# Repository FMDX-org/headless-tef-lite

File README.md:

# TEF668X Headless Lite USB Tuner

USB radio tuner based on the STM32F072 MCU and TEF668X/V205 RF receiver with digital audio output over USB. This is the lite variant of our [Headless USB tuner](https://github.com/FMDX-org/tef668x-headless-usb-tuner). It is more compact, with a simplified RF input path and only one antenna input for AM/FM.

This design is optimized as a cost-efficient solution tailored for automated PCBA (Printed Circuit Board Assembly) processes.

Copyright (C) 2025 FMDX.org

You may redistribute and modify this source under the terms of the CERN-OHL-W v2 (see LICENSE file).

# Credits 

- Konrad Kosmatka - HW & FW architecture and development
- Sjef Verhoeven - HW development
- Marek Kraus - HW & FW prototyping
- Marek Farkaš - testing and integration with FM-DX Webserver
- Przemysław Korpas - HW consultation, reviews
- Sebastian Białkowski - HW consultation, reviews

# Firmware

The firmware is available in a separate repository: [FM-DX-Tuner](https://github.com/kkonradpl/FM-DX-Tuner).

Firmware dependencies:
- Board: STM32 MCU Based Boards ([STM32duino](https://github.com/stm32duino)) - download using board manager
- Library: [TinyUSB](https://github.com/hathach/tinyusb) - install manually to the Arduino libraries

During first firmware flashing, short BOOT to 3.3V, plug the USB cable and flash using Arduino IDE (DFU method). Once the firmware is running, it is not necessary to manually short BOOT pin. See [tef-bootloader](https://github.com/kkonradpl/tef-bootloader).

# Audio output

The baseline version of the tuner supports only digital audio over USB. You can access analog audio via the L and R solder points, but this output is unbuffered. Therefore, you will need to build an additional electronic circuit to achieve proper audio output.

# Important remarks

- TEF6687/V205 (F8705) chip is recommended for the best performance (FMSI, FULL SCAN RDS).
- RF circuits should contain NP0 (C0G) capacitors.
- Only V205 version of TEF668X are supported on this design!
- All capacitors and resistors are 0402.

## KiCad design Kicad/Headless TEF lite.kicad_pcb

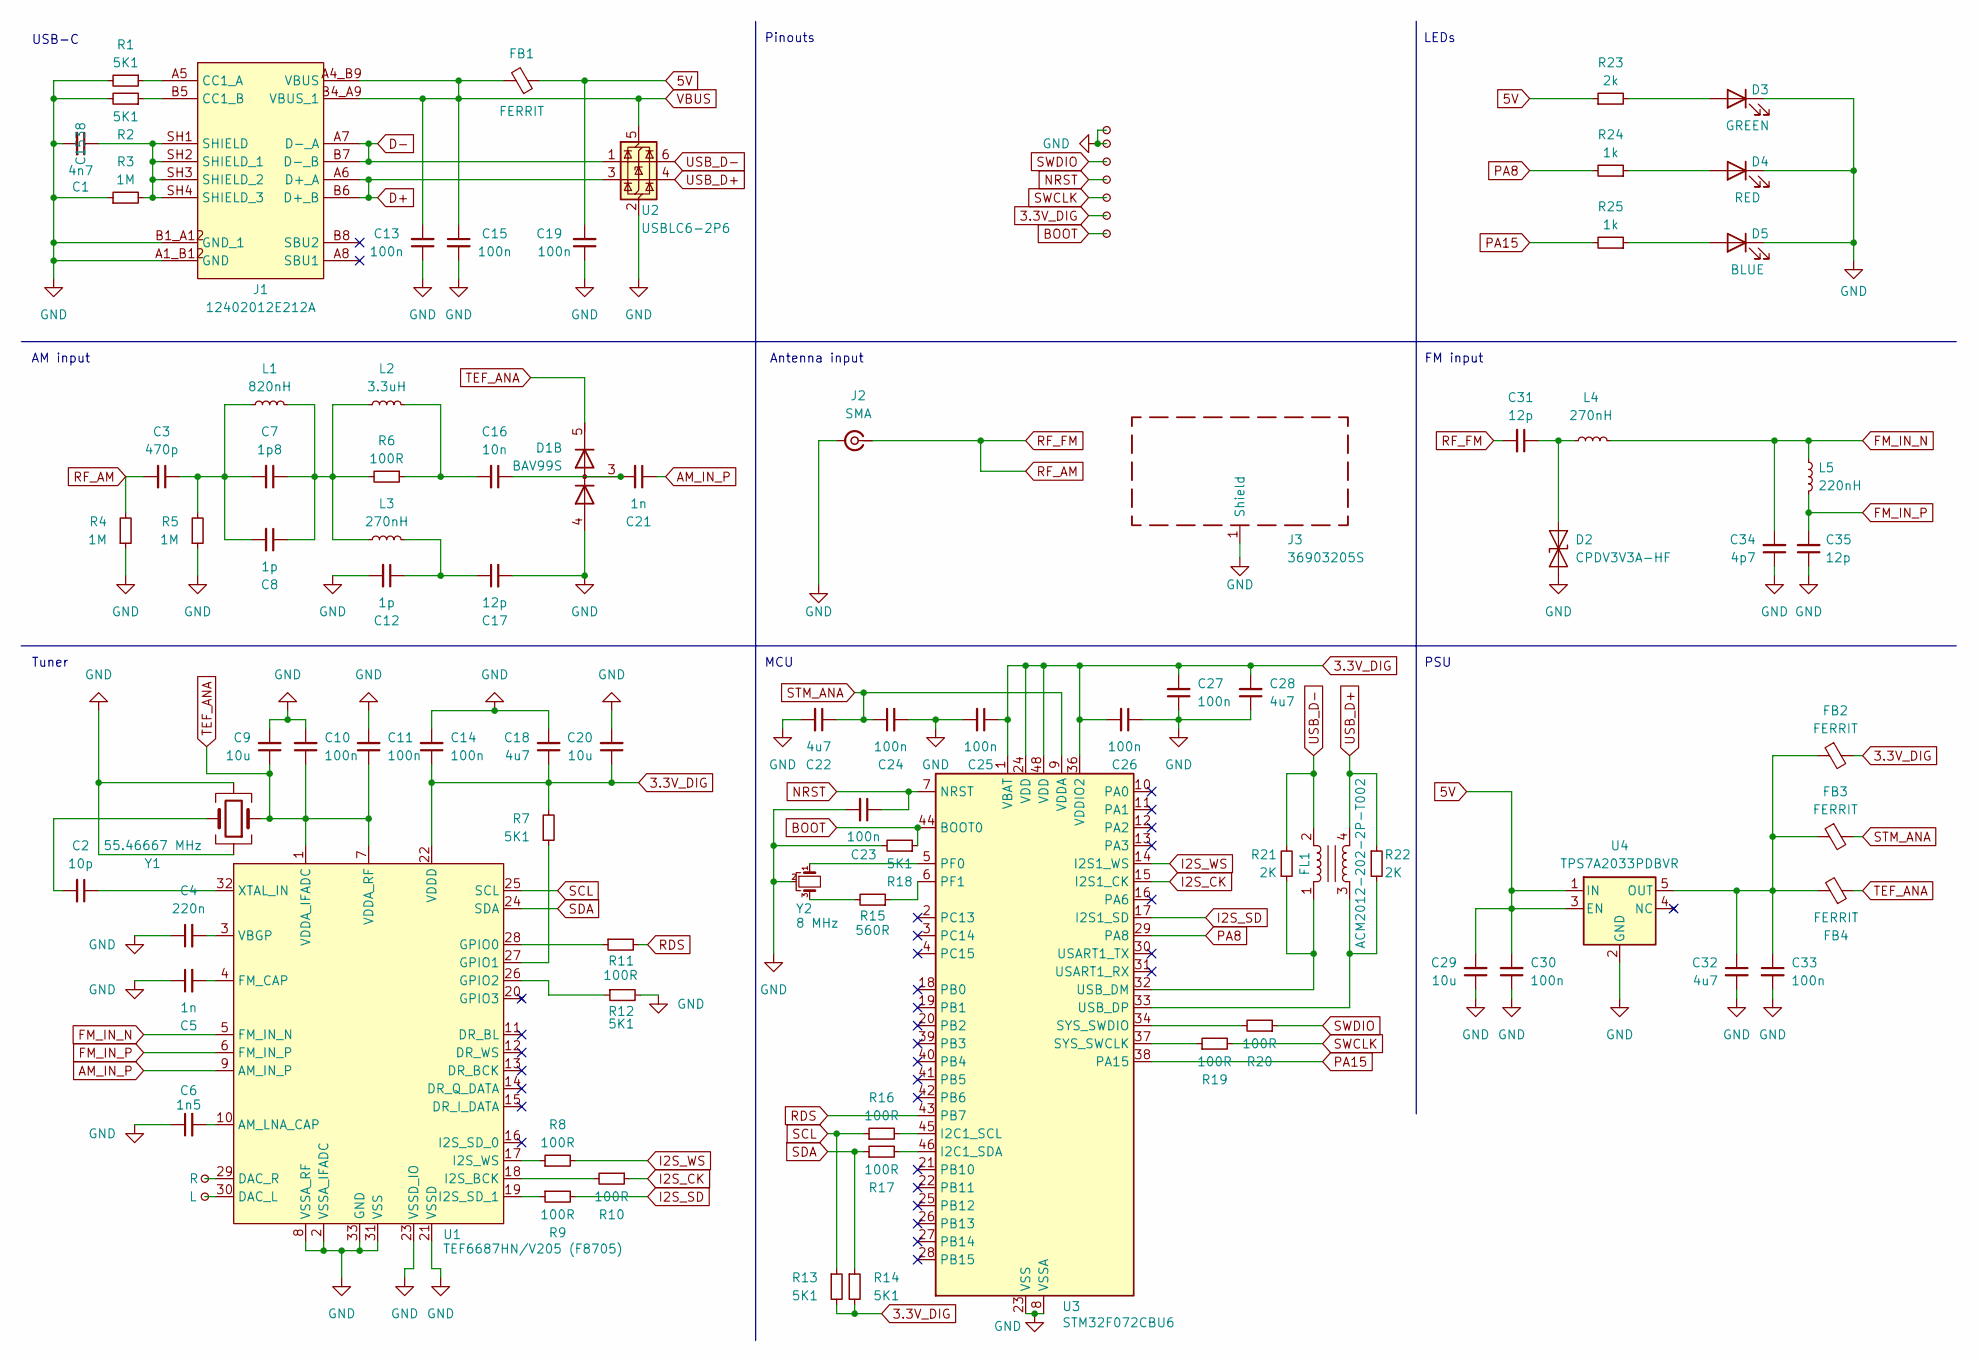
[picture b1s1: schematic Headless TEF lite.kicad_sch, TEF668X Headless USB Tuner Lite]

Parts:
C1: 4n7; C_0402_1005Metric
C2: 10p; C_0402_1005Metric
C3: 470p; C_0402_1005Metric
C4: 220n; C_0402_1005Metric
C5, C21: 1n; C_0402_1005Metric
C6: 1n5; C_0402_1005Metric
C7: 1p8; C_0402_1005Metric
C8, C12: 1p; C_0402_1005Metric
C9, C20, C29: 10u; C_0402_1005Metric
C10, C11, C13, C14, C15, C19, C23, C24, C25, C26, C27, C30, C33: 100n; C_0402_1005Metric
C16: 10n; C_0402_1005Metric
C17, C31, C35: 12p; C_0402_1005Metric
C18, C22, C28, C32: 4u7; C_0402_1005Metric
C34: 4p7; C_0402_1005Metric
D1: BAV99S; SOT-363_SC-70-6
D2: CPDV3V3A-HF; D_SOD-323
D3: GREEN; LED_0402_1005Metric
D4: RED; LED_0402_1005Metric
D5: BLUE; LED_0402_1005Metric
FB1, FB2, FB3, FB4: FERRIT; L_0402_1005Metric
FL1: ACM2012-202-2P-T002; USB_Filter_0805
J1: 12402012E212A
J2: SMA; SMA_Molex_73251-2120_EdgeMount_Horizontal
J3: 36903205S; 36103205S
L1: 820nH; L_0402_1005Metric
L2: 3.3uH; L_0402_1005Metric
L3, L4: 270nH; L_0402_1005Metric
L5: 220nH; L_0402_1005Metric
R1, R2, R7, R12, R13, R14, R18: 5K1; R_0402_1005Metric
R3, R4, R5: 1M; R_0402_1005Metric
R6, R8, R9, R10, R11, R16, R17, R19, R20: 100R; R_0402_1005Metric
R15: 560R; R_0402_1005Metric
R21, R22: 2K; R_0402_1005Metric
R23: 2k; R_0402_1005Metric
R24, R25: 1k; R_0402_1005Metric
TP1: R; TestPoint_Pad_D1.0mm
TP2: L; TestPoint_Pad_D1.0mm
TP3, TP4, TP5, TP6, TP7, TP8, TP9: TestPoint_Pad_D1.0mm
U1: TEF6687HN/V205 (F8705); QFN-32-1EP_5x5mm_P0.5mm_EP3.3x3.3mm_ThermalVias
U2: USBLC6-2P6; SOT-666
U3: STM32F072CBU6; VQFN-48-1EP_7x7mm_P0.5mm_EP4.1x4.1mm_ThermalVias
U4: TPS7A2033PDBVR; SOT-23-5
Y1: 55.46667 MHz; Crystal_SMD_3225-4Pin_3.2x2.5mm
Y2: 8 MHz; Resonator_SMD_Murata_CSTxExxV-3Pin_3.0x1.1mm

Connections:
3.3V_DIG: C14.1, C18.1, C20.1, C25.1, C26.2, C27.2, C28.2, FB2.2, R7.2, R13.2, R14.2, TP8.1, U1.22 (VDDD), U3.1 (VBAT), U3.24 (VDD), U3.36 (VDDIO2), U3.48 (VDD)
5V: C19.2, C29.2, C30.2, FB1.1, R23.1, U4.1 (IN), U4.3 (EN)
AM_IN_P: C21.1, U1.9 (AM_IN_P)
BOOT: R18.1, TP9.1, U3.44 (BOOT0)
D+: J1.A6 (D+_A), J1.B6 (D+_B), U2.3 (I/O2)
D-: J1.A7 (D-_A), J1.B7 (D-_B), U2.1 (I/O1)
FM_IN_N: C34.2, L4.2, L5.1, U1.5 (FM_IN_N)
FM_IN_P: C35.2, L5.2, U1.6 (FM_IN_P)
GND: C1.2, C4.1, C5.1, C6.1, C9.2, C10.2, C11.2, C12.2, C13.1, C14.2, C15.2, C17.2, C18.2, C19.1, C20.2, C22.2, C23.2, C24.2, C25.2, C26.1, C27.1, C28.1, C29.1, C30.1, C32.2, C33.2, C34.1, C35.1, D1.4 (A3), D2.2 (A2), D3.1 (K), D4.1 (K), D5.1 (K), J1.A1_B12 (GND), J1.B1_A12 (GND_1), J2.2 (Ext), J3.1 (Shield), R1.2, R2.2, R3.1, R4.1, R5.1, R12.2, R18.2, TP3.1, TP4.1, U1.2 (VSSA_IFADC), U1.8 (VSSA_RF), U1.21 (VSSD), U1.23 (VSSD_IO), U1.31 (VSS), U1.33 (GND), U2.2 (GND), U3.8 (VSSA), U3.23 (VSS), U3.35 (VSS), U3.47 (VSS), U3.49 (GND), U4.2 (GND), Y1.2, Y1.4, Y2.2
I2S_CK: R10.1, U3.15 (I2S1_CK)
I2S_SD: R9.2, U3.17 (I2S1_SD)
I2S_WS: R8.2, U3.14 (I2S1_WS)
NRST: C23.1, TP6.1, U3.7 (NRST)
unnamed: C2.2, Y1.3
unnamed: C3.1, C7.2, C8.2, L1.1, R5.2
unnamed: C7.1, C8.1, L1.2, L2.1, L3.1, R6.2
unnamed: C12.1, C17.1, L3.2
unnamed: C16.2, L2.2, R6.1
unnamed: C16.1, C21.2, D1.3 (K1A2)
unnamed: C31.1, D2.1 (A1), L4.1
unnamed: D3.2 (A), R23.2
unnamed: D4.2 (A), R24.1
unnamed: D5.2 (A), R25.1
unnamed: J1.A5 (CC1_A), R1.1
unnamed: J1.B5 (CC1_B), R2.1
unnamed: C1.1, J1.SH1 (SHIELD), J1.SH2 (SHIELD_1), J1.SH3 (SHIELD_2), J1.SH4 (SHIELD_3), R3.2
unnamed: R15.2, Y2.3
unnamed: C6.2, U1.10 (AM_LNA_CAP)
unnamed: TP2.1, U1.30 (DAC_L)
unnamed: TP1.1, U1.29 (DAC_R)
unnamed: C5.2, U1.4 (FM_CAP)
unnamed: R11.1, U1.28 (GPIO0)
unnamed: R7.1, U1.27 (GPIO1)
unnamed: R12.1, U1.26 (GPIO2)
unnamed: R10.2, U1.18 (I2S_BCK)
unnamed: R9.1, U1.19 (I2S_SD_1)
unnamed: R8.1, U1.17 (I2S_WS)
unnamed: C4.2, U1.3 (VBGP)
unnamed: C2.1, U1.32 (XTAL_IN)
unnamed: FL1.1, R21.1, U3.32 (USB_DM)
unnamed: FL1.3, R22.2, U3.33 (USB_DP)
unnamed: R20.2, U3.34 (SYS_SWDIO)
unnamed: R19.1, U3.37 (SYS_SWCLK)
unnamed: R16.2, U3.45 (I2C1_SCL)
unnamed: R17.2, U3.46 (I2C1_SDA)
unnamed: U3.5 (PF0), Y2.1
unnamed: R15.1, U3.6 (PF1)
unnamed: C32.1, C33.1, FB2.1, FB3.1, FB4.2, U4.5 (OUT)
PA8: R24.2, U3.29 (PA8)
PA15: R25.2, U3.38 (PA15)
RDS: R11.2, U3.43 (PB7)
RF_AM: C3.2, C31.2, J2.1 (In), R4.2
SCL: R13.1, R16.1, U1.25 (SCL)
SDA: R14.1, R17.1, U1.24 (SDA)
STM_ANA: C22.1, C24.1, FB3.2, U3.9 (VDDA)
SWCLK: R19.2, TP7.1
SWDIO: R20.1, TP5.1
TEF_ANA: C9.1, C10.1, C11.1, D1.5 (K4), FB4.1, U1.1 (VDDA_IFADC), U1.7 (VDDA_RF), Y1.1
USB_D+: FL1.4, R22.1, U2.4 (I/O2)
USB_D-: FL1.2, R21.2, U2.6 (I/O1)
VBUS: C13.2, C15.1, FB1.2, J1.A4_B9 (VBUS), J1.B4_A9 (VBUS_1), U2.5 (VBUS)

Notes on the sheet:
PSU
Pinouts
AM input
Antenna input
MCU
Tuner
USB-C
FM input
LEDs

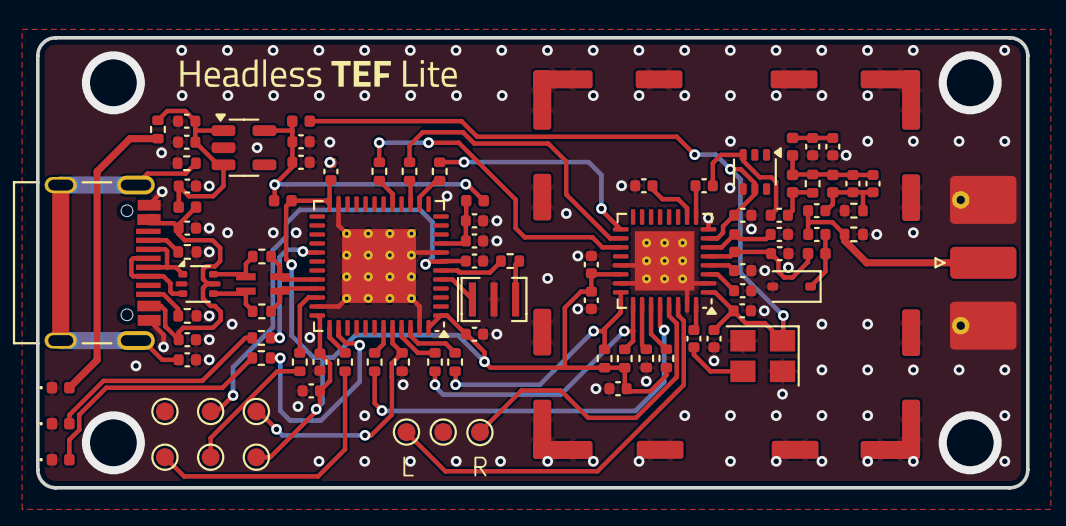
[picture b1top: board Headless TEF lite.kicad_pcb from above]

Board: 2 copper layers, 55.0 x 25.0 mm, 93 parts (0 on the bottom side), 61 nets.

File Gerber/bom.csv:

Designator,Footprint,Quantity,Value,LCSC Part #
C1,0402,1,4n7,
"C10, C11, C13, C14, C15, C19, C23, C24, C25, C26, C27, C30, C33",0402,13,100n,
"C12, C8",0402,2,1p,
C16,0402,1,10n,
"C17, C31, C35",0402,3,12p,
"C18, C22, C28, C32",0402,4,4u7,
C2,0402,1,10p,
"C20, C29, C9",0402,3,10u,
"C21, C5",0402,2,1n,
C3,0402,1,470p,
C34,0402,1,4p7,
C4,0402,1,220n,
C6,0402,1,1n5,
C7,0402,1,1p8,
D1,SOT-363_SC-70-6,1,BAV99S,
D2,D_SOD-323,1,CPDV3V3A-HF,
D3,0402,1,GREEN,
D4,0402,1,RED,
D5,0402,1,BLUE,
"FB1, FB2, FB3, FB4",0402,4,FERRIT,
FL1,USB_Filter_0805,1,ACM2012-202-2P-T002,
J1,12402012E212A,1,12402012E212A,
J2,SMA_Molex_73251-2120_EdgeMount_Horizontal,1,SMA,
J3,36103205S,1,36903205S,
L1,0402,1,820nH,
L2,0402,1,3.3uH,
"L3, L4",0402,2,270nH,
L5,0402,1,220nH,
"R1, R12, R13, R14, R18, R2, R7",0402,7,5K1,
"R10, R11, R16, R17, R19, R20, R6, R8, R9",0402,9,100R,
R15,0402,1,560R,
"R21, R22, R23",0402,3,2K,
"R24, R25",0402,2,1k,
"R3, R4, R5",0402,3,1M,
TP1,TestPoint_Pad_D1.0mm,1,R,
TP2,TestPoint_Pad_D1.0mm,1,L,
"TP3, TP4, TP5, TP6, TP7, TP8, TP9",TestPoint_Pad_D1.0mm,7,~,
U1,QFN-32-1EP_5x5mm_P0.5mm_EP3.3x3.3mm_ThermalVias,1,TEF6687HN/V205 (F8705),
U2,SOT-666,1,USBLC6-2P6,
U3,VQFN-48-1EP_7x7mm_P0.5mm_EP4.1x4.1mm_ThermalVias,1,STM32F072CBU6,
U4,SOT-23-5,1,TPS7A2033PDBVR,
Y1,Crystal_SMD_3225-4Pin_3.2x2.5mm,1,55.46667 MHz,
Y2,Resonator_SMD_Murata_CSTxExxV-3Pin_3.0x1.1mm,1,8 MHz,

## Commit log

2025-05-07 File upload
2025-05-07 Upload schematics
2025-05-21 Create LICENCE
2025-05-28 3d case
2025-06-09 Update STL
